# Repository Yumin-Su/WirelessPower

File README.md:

# WirelessPower
EAGLE PCB files for Wireless Power Team

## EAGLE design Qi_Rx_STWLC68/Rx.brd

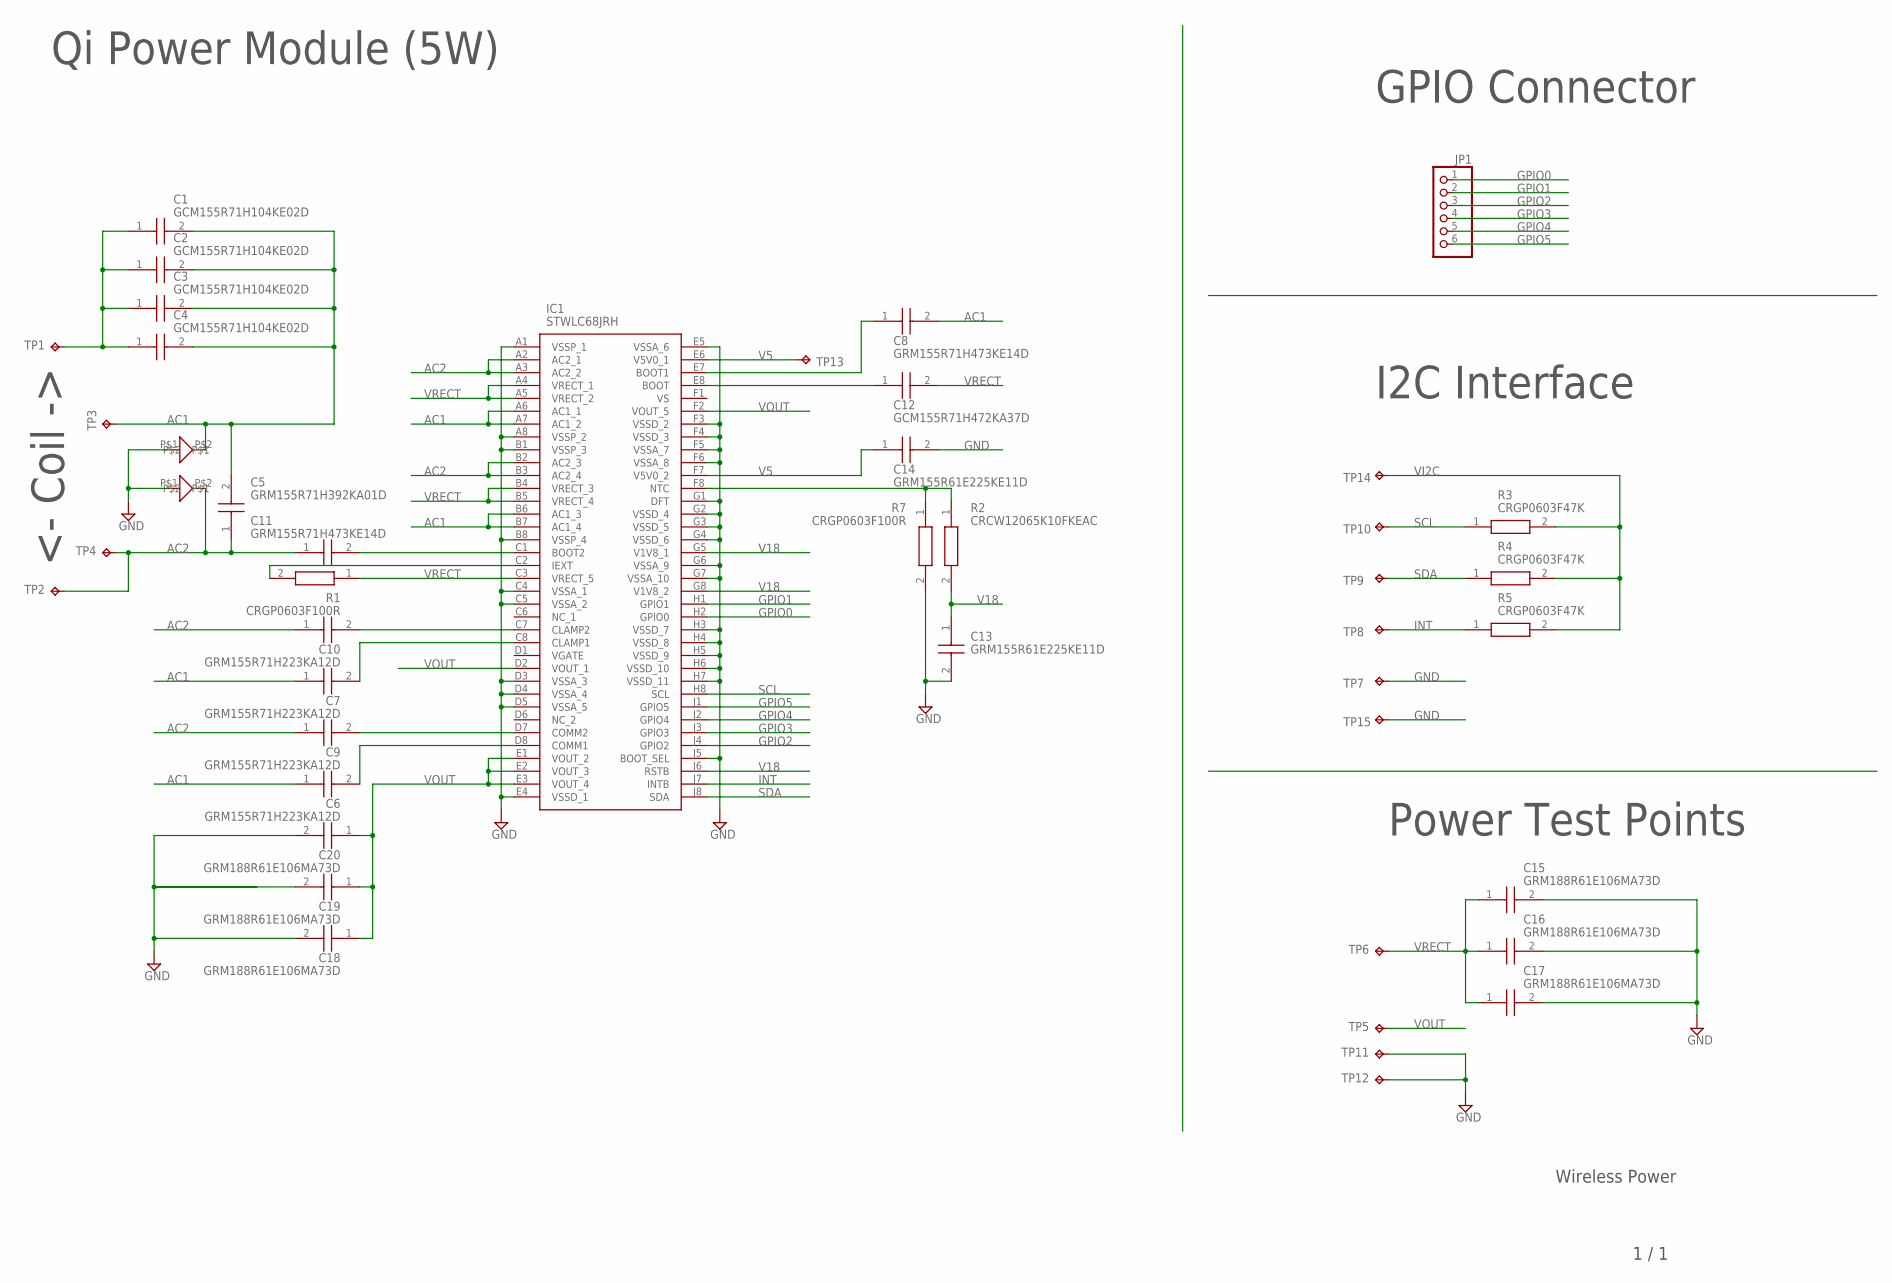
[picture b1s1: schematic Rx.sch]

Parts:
C1, C2, C3, C4: GCM155R71H104KE02D; CAPC1005X55N
C5: GRM155R71H392KA01D; CAPC1005X55N
C6, C7, C9, C10: GRM155R71H223KA12D; CAPC1005X55N
C8, C11: GRM155R71H473KE14D; CAPC1005X55N
C12: GCM155R71H472KA37D; CAPC1005X55N
C13, C14: GRM155R61E225KE11D; CAPC1005X55N
C15, C16, C17, C18, C19, C20: GRM188R61E106MA73D; CAPC1608X90N
IC1: STWLC68JRH; BGA72C40P9X9_441X376X58
JP1: PINHD-1X6; 1X06
R1, R7: CRGP0603F100R; RESC1608X55N
R2: CRCW12065K10FKEAC; RESC3216X60N
R3, R4, R5: CRGP0603F47K; RESC1608X55N
TP1, TP2, TP3, TP4, TP5, TP6, TP7, TP8, TP9, TP10, TP11, TP12, TP13, TP14, TP15: TPPAD1-13; P1-13
U$1, U$2: SMAJ16A

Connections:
AC1: C1.2, C2.2, C3.2, C4.2, C5.2, C6.1, C7.1, C8.2, IC1.A6 (AC1_1), IC1.A7 (AC1_2), IC1.B6 (AC1_3), IC1.B7 (AC1_4), TP3.TP, U$1.P$2
AC2: C5.1, C9.1, C10.1, C11.1, IC1.A2 (AC2_1), IC1.A3 (AC2_2), IC1.B2 (AC2_3), IC1.B3 (AC2_4), TP2.TP, TP4.TP, U$2.P$2
GND: C13.2, C14.2, C15.2, C16.2, C17.2, C18.2, C19.2, C20.2, IC1.A1 (VSSP_1), IC1.A8 (VSSP_2), IC1.B1 (VSSP_3), IC1.B8 (VSSP_4), IC1.C4 (VSSA_1), IC1.C5 (VSSA_2), IC1.D3 (VSSA_3), IC1.D4 (VSSA_4), IC1.D5 (VSSA_5), IC1.E4 (VSSD_1), IC1.E5 (VSSA_6), IC1.F3 (VSSD_2), IC1.F4 (VSSD_3), IC1.F5 (VSSA_7), IC1.F6 (VSSA_8), IC1.G1 (DFT), IC1.G2 (VSSD_4), IC1.G3 (VSSD_5), IC1.G4 (VSSD_6), IC1.G6 (VSSA_9), IC1.G7 (VSSA_10), IC1.H3 (VSSD_7), IC1.H4 (VSSD_8), IC1.H5 (VSSD_9), IC1.H6 (VSSD_10), IC1.H7 (VSSD_11), IC1.J5 (BOOT_SEL), R7.2, TP7.TP, TP11.TP, TP12.TP, TP15.TP, U$1.P$1, U$2.P$1
GPIO0: IC1.H2 (GPIO0), JP1.1
GPIO1: IC1.H1 (GPIO1), JP1.2
GPIO2: IC1.J4 (GPIO2), JP1.3
GPIO3: IC1.J3 (GPIO3), JP1.4
GPIO4: IC1.J2 (GPIO4), JP1.5
GPIO5: IC1.J1 (GPIO5), JP1.6
INT: IC1.J7 (INTB), R5.1, TP8.TP
unnamed: C6.2, IC1.D8 (COMM1)
unnamed: C7.2, IC1.C8 (CLAMP1)
unnamed: C8.1, IC1.E7 (BOOT1)
unnamed: C1.1, C2.1, C3.1, C4.1, TP1.TP
unnamed: C11.2, IC1.C1 (BOOT2)
unnamed: C10.2, IC1.C7 (CLAMP2)
unnamed: C9.2, IC1.D7 (COMM2)
unnamed: C12.1, IC1.E8 (BOOT)
unnamed: IC1.C2 (IEXT), R1.2
unnamed: IC1.F8 (NTC), R2.1, R7.1
SCL: IC1.H8 (SCL), R3.1, TP10.TP
SDA: IC1.J8 (SDA), R4.1, TP9.TP
V5: C14.1, IC1.E6 (V5V0_1), IC1.F7 (V5V0_2), TP13.TP
V18: C13.1, IC1.G5 (V1V8_1), IC1.G8 (V1V8_2), IC1.J6 (RSTB), R2.2
VI2C: R3.2, R4.2, R5.2, TP14.TP
VOUT: C18.1, C19.1, C20.1, IC1.D2 (VOUT_1), IC1.E1 (VOUT_2), IC1.E2 (VOUT_3), IC1.E3 (VOUT_4), IC1.F2 (VOUT_5), TP5.TP
VRECT: C12.2, C15.1, C16.1, C17.1, IC1.A4 (VRECT_1), IC1.A5 (VRECT_2), IC1.B4 (VRECT_3), IC1.B5 (VRECT_4), IC1.C3 (VRECT_5), R1.1, TP6.TP

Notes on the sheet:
1 / 1
Wireless Power
GPIO Connector
Qi Power Module (5W)
I2C Interface
Power Test Points
<- Coil ->

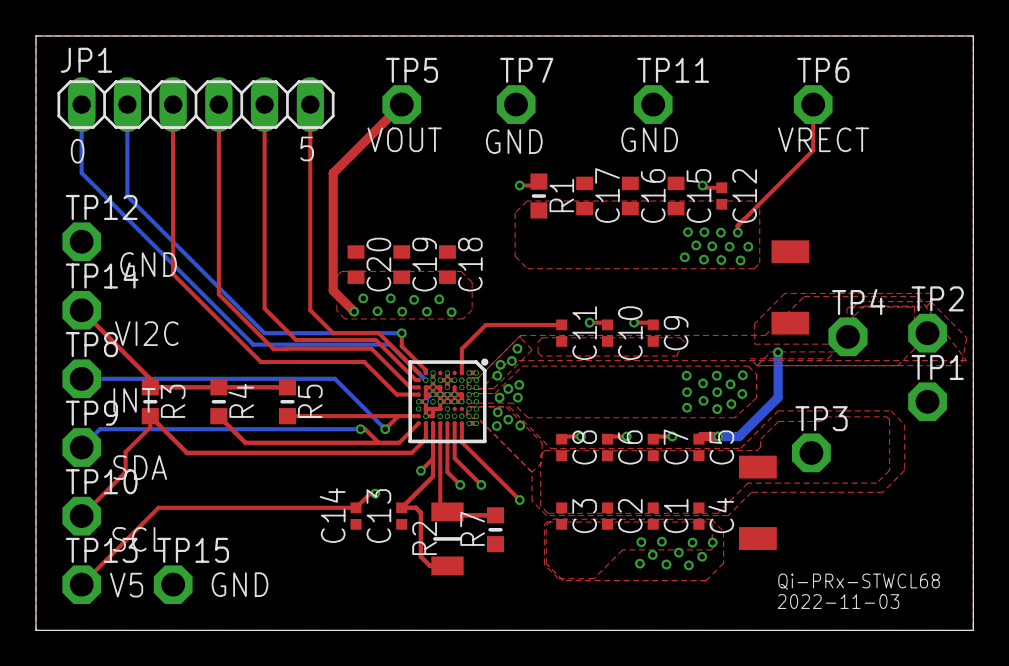
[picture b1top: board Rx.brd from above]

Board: 4 copper layers, 52.1 x 33.0 mm, 45 parts (0 on the bottom side), 27 nets.

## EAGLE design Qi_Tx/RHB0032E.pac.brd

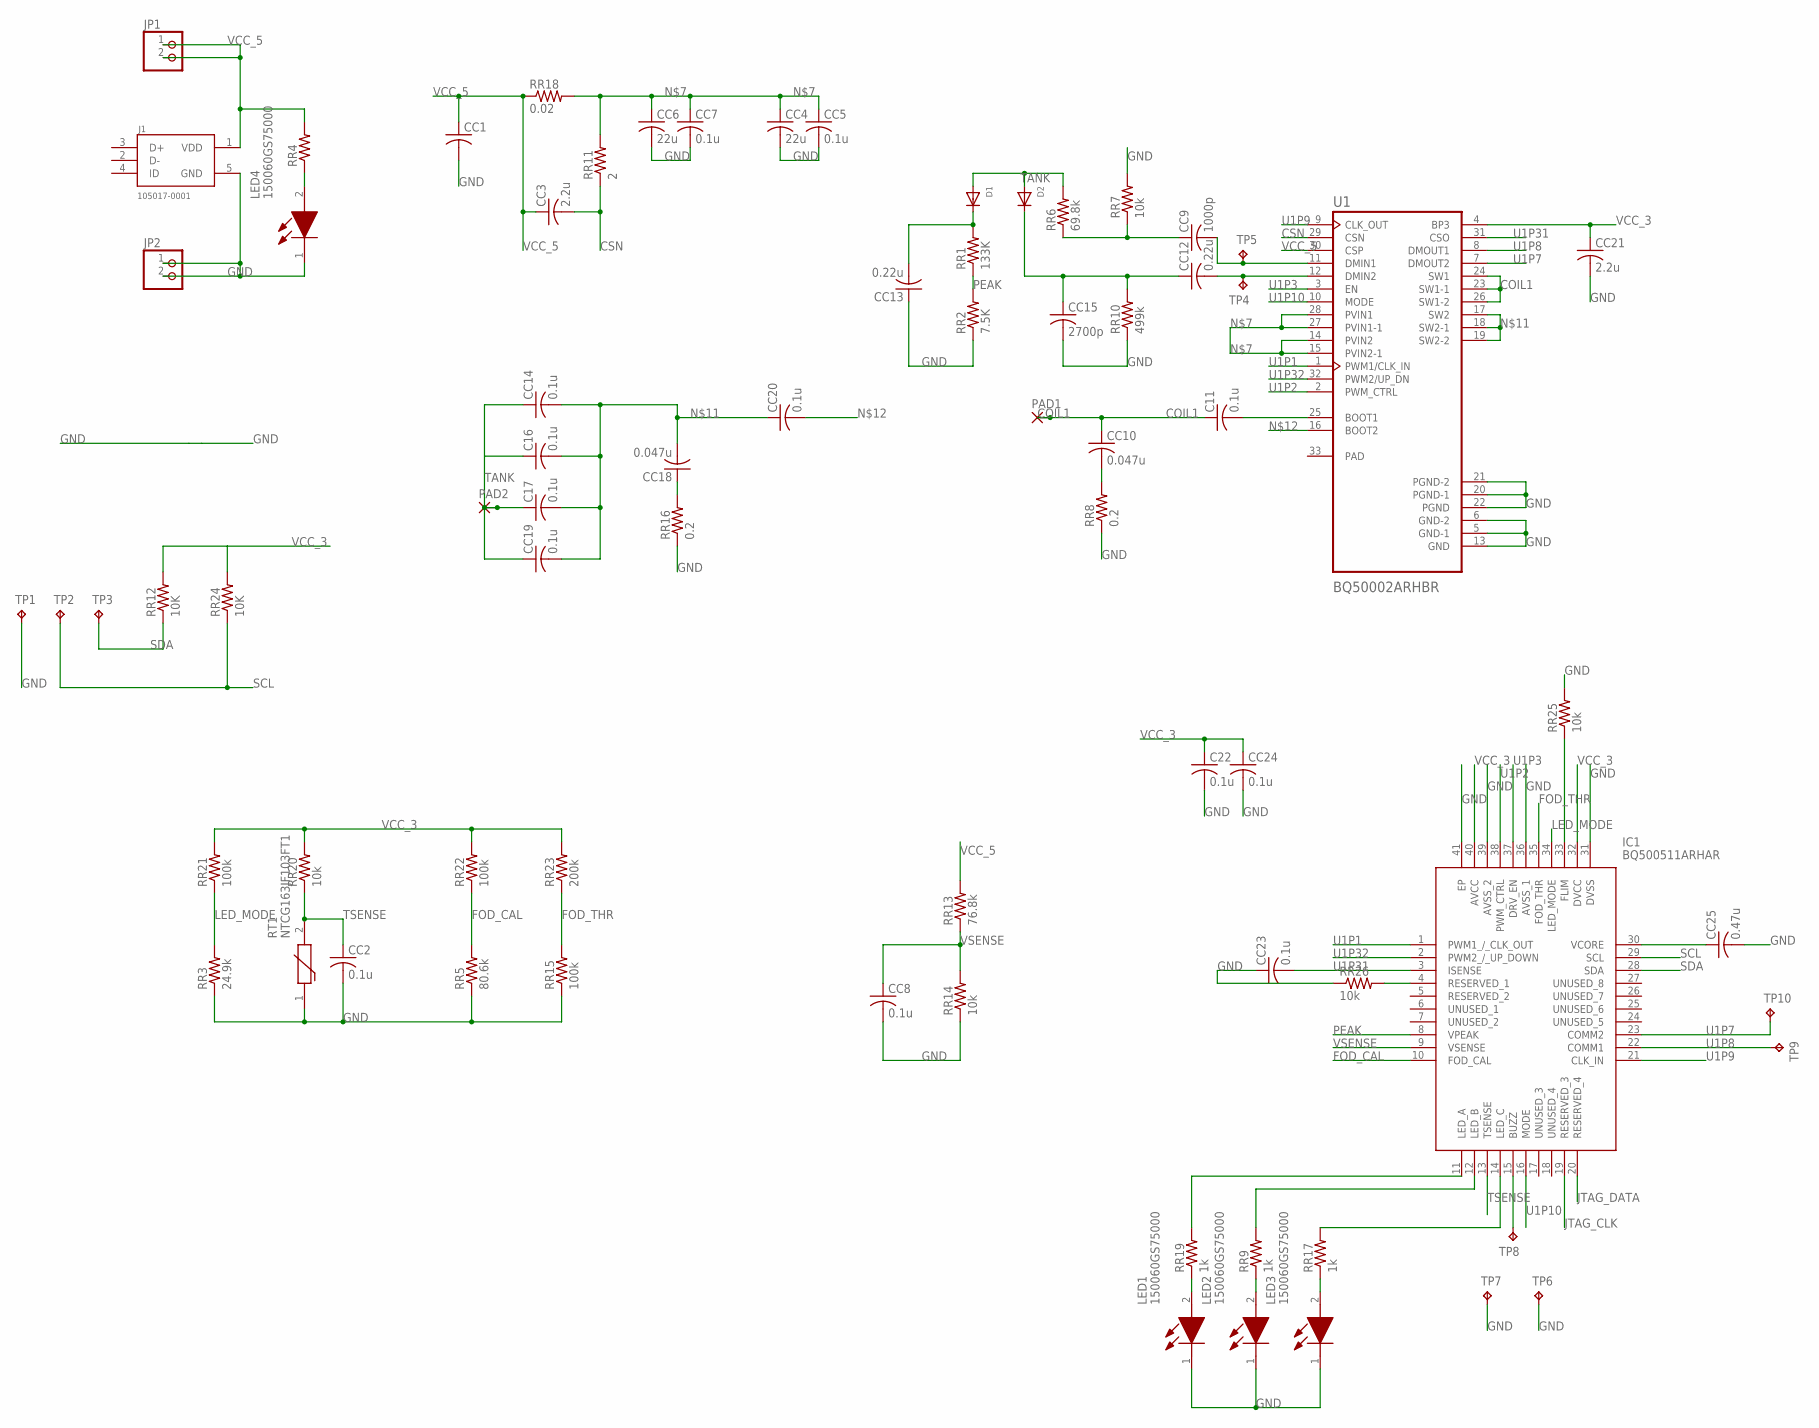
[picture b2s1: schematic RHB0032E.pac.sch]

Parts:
C11, C16, C17, C22: 0.1u; C0402
CC1: C-USC0402; C0402
CC2, CC5, CC7, CC8, CC14, CC19, CC20, CC23, CC24: 0.1u; C0402
CC3, CC21: 2.2u; C0402
CC4, CC6: 22u; C0402
CC9: 1000p; C0402
CC10, CC18: 0.047u; C0402
CC12, CC13: 0.22u; C0402
CC15: 2700p; C0402
CC25: 0.47u; C0402
D1, D2: DIODESOD-523; SOD-523
IC1: BQ500511ARHAR; QFN50P600X600X100-41N
J1: 105017-0001; MOLEX_105017-0001
JP1, JP2: PINHD-1X2; 1X02
LED1, LED2, LED3, LED4: 150060GS75000; LEDC1608X80N
PAD1, PAD2: SMD2; SMD1,27-2,54
RR1: 133K; R0603
RR2: 7.5K; R0603
RR3: 24.9k; R0603
RR4: R-US_R0603; R0603
RR5: 80.6k; R0603
RR6: 69.8k; R0603
RR7, RR14, RR20, RR25, RR26: 10k; R0603
RR8, RR16: 0.2; R0603
RR9, RR17, RR19: 1k; R0603
RR10: 499k; R0603
RR11: 2; R0603
RR12, RR24: 10K; R0603
RR13: 76.8k; R0603
RR15, RR21, RR22: 100k; R0603
RR18: 0.02; R0603
RR23: 200k; R0603
RT1: NTCG163JF103FT1; THRMC1608X90N
TP1, TP2, TP3, TP4, TP5, TP6, TP7, TP8, TP9, TP10: TPB1,27; B1,27
U1: BQ50002ARHBR; IC_ADS125H01IRHBT

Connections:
COIL1: C11.1, CC10.1, PAD1.1, U1.23 (SW1-1), U1.24 (SW1), U1.26 (SW1-2)
CSN: CC3.2, RR11.1, U1.29 (CSN)
FOD_CAL: IC1.10 (FOD_CAL), RR5.2, RR22.1
FOD_THR: IC1.35 (FOD_THR), RR15.2, RR23.1
GND: C22.2, CC1.2, CC2.2, CC4.2, CC5.2, CC6.2, CC7.2, CC8.2, CC13.1, CC15.2, CC21.2, CC23.1, CC24.2, CC25.2, IC1.31 (DVSS), IC1.36 (AVSS_1), IC1.39 (AVSS_2), IC1.41 (EP), J1.5 (GND), JP2.1, JP2.2, LED1.1 (K), LED2.1 (K), LED3.1 (K), LED4.1 (K), RR2.1, RR3.1, RR5.1, RR7.2, RR8.1, RR10.1, RR14.1, RR15.1, RR16.1, RR25.2, RR26.1, RT1.1, TP1.TP, TP6.TP, TP7.TP, U1.5 (GND-1), U1.6 (GND-2), U1.13 (GND), U1.20 (PGND-1), U1.21 (PGND-2), U1.22 (PGND)
JTAG_CLK: IC1.19 (RESERVED_3)
JTAG_DATA: IC1.20 (RESERVED_4)
LED_MODE: IC1.34 (LED_MODE), RR3.2, RR21.1
unnamed: CC12.2, TP4.TP, U1.12 (DMIN2)
unnamed: CC12.1, CC15.1, D2.K (C), RR10.2
unnamed: CC13.2, D1.K (C), RR1.2
unnamed: CC9.2, TP5.TP, U1.11 (DMIN1)
unnamed: CC9.1, RR6.1, RR7.1
unnamed: CC4.1, CC5.1, CC6.1, CC7.1, RR11.2, RR18.2, U1.14 (PVIN2), U1.15 (PVIN2-1), U1.27 (PVIN1-1), U1.28 (PVIN1)
unnamed: IC1.15 (BUZZ), TP8.TP
unnamed: C11.2, U1.25 (BOOT1)
unnamed: CC10.2, RR8.2
unnamed: C16.2, C17.2, CC14.2, CC18.2, CC19.2, CC20.1, U1.17 (SW2), U1.18 (SW2-1), U1.19 (SW2-2)
unnamed: CC20.2, U1.16 (BOOT2)
unnamed: CC25.1, IC1.30 (VCORE)
unnamed: LED1.2 (A), RR19.1
unnamed: CC18.1, RR16.2
unnamed: LED2.2 (A), RR9.1
unnamed: LED3.2 (A), RR17.1
unnamed: IC1.33 (FLIM), RR25.1
unnamed: IC1.11 (LED_A), RR19.2
unnamed: IC1.12 (LED_B), RR9.2
unnamed: IC1.14 (LED_C), RR17.2
unnamed: IC1.4 (RESERVED_1), RR26.2
unnamed: LED4.2 (A), RR4.1
PEAK: IC1.8 (VPEAK), RR1.1, RR2.2
SCL: IC1.29 (SCL), RR24.1, TP2.TP
SDA: IC1.28 (SDA), RR12.1, TP3.TP
TANK: C16.1, C17.1, CC14.1, CC19.1, D1.A, D2.A, PAD2.1, RR6.2
TSENSE: CC2.1, IC1.13 (TSENSE), RR20.1, RT1.2
U1P1: IC1.1 (PWM1_/_CLK_OUT), U1.1 (PWM1/CLK_IN)
U1P2: IC1.38 (PWM_CTRL), U1.2 (PWM_CTRL)
U1P3: IC1.37 (DRV_EN), U1.3 (EN)
U1P7: IC1.23 (COMM2), TP10.TP, U1.7 (DMOUT2)
U1P8: IC1.22 (COMM1), TP9.TP, U1.8 (DMOUT1)
U1P9: IC1.21 (CLK_IN), U1.9 (CLK_OUT)
U1P10: IC1.16 (MODE), U1.10 (MODE)
U1P31: CC23.2, IC1.3 (ISENSE), U1.31 (CSO)
U1P32: IC1.2 (PWM2_/_UP_DOWN), U1.32 (PWM2/UP_DN)
VCC_3: C22.1, CC21.1, CC24.1, IC1.32 (DVCC), IC1.40 (AVCC), RR12.2, RR20.2, RR21.2, RR22.2, RR23.2, RR24.2, U1.4 (BP3)
VCC_5: CC1.1, CC3.1, J1.1 (VDD), JP1.1, JP1.2, RR4.2, RR13.2, RR18.1, U1.30 (CSP)
VSENSE: CC8.1, IC1.9 (VSENSE), RR13.1, RR14.2

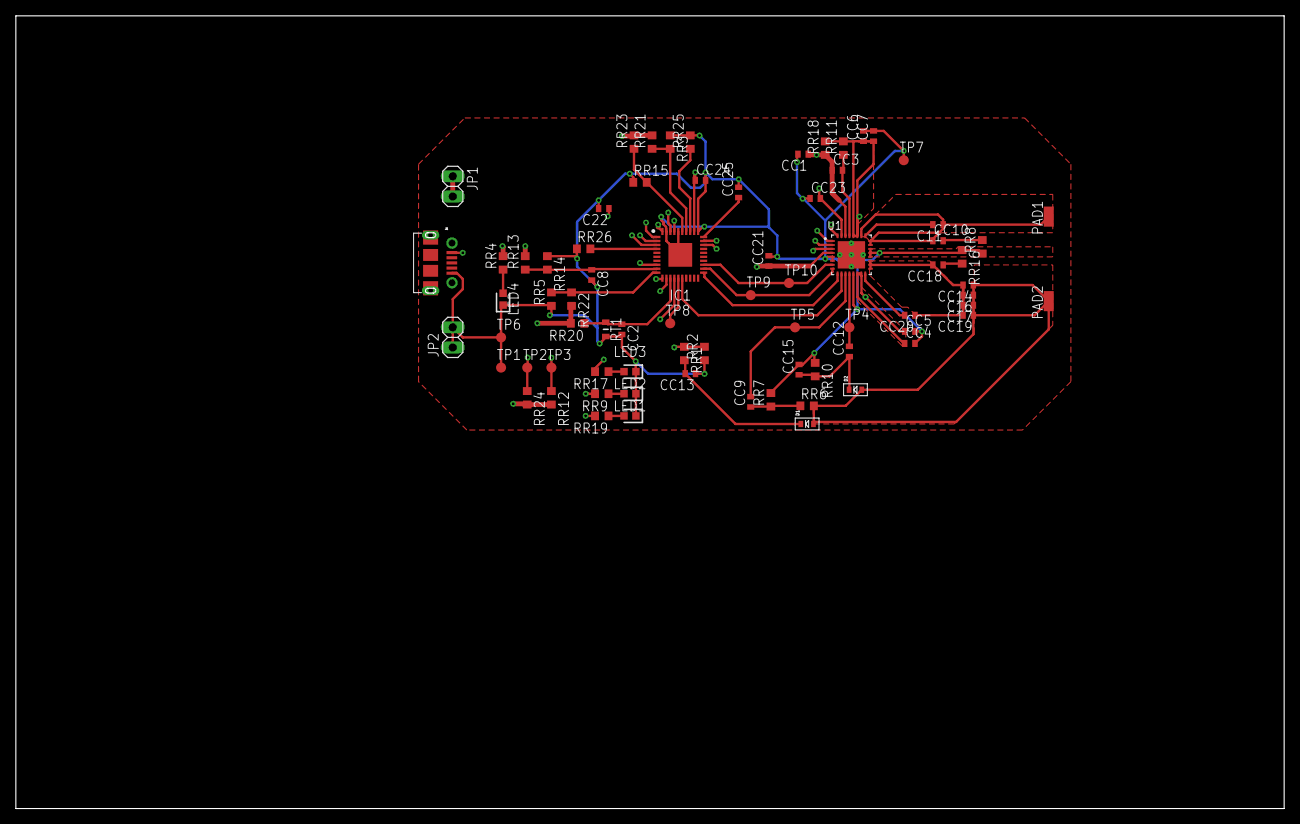
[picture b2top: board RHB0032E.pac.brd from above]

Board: 4 copper layers, 160.0 x 100.0 mm, 75 parts (0 on the bottom side), 45 nets.

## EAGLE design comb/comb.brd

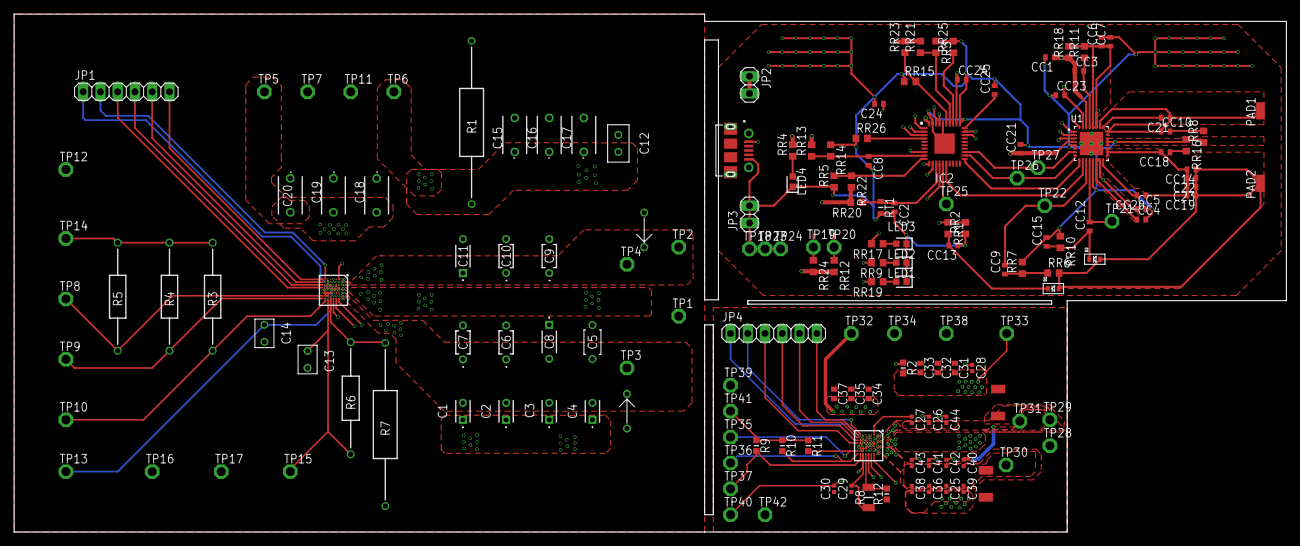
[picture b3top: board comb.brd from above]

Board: 4 copper layers, 187.1 x 76.2 mm, 167 parts (0 on the bottom side), 99 nets.

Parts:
C1, C2, C3, C4: K104K15X7RF5UL2
C5: RCE5C1H392J0K1H03B; RCER71H104K0K1H03B
C6, C7, C9, C10: K223K15X7RF53H5G
C8, C11: K473K15X0UH53H5H
C12: RDE5C2J472J2K1H03B; RCE5C1H104J2A2H03B
C13, C14: RHS7G2A222J1DGH01A; RHS7G2A182J1A2H01B
C15, C16, C17, C18, C19, C20: FG26X7R1E106KRT06; FG26
C21, C22, C23, C24: 0.1u; C0402
C25, C36, C38, C39: GCM155R71H104KE02D; CAPC1005X55N
C26, C41, C42, C44: GRM155R71H223KA12D; CAPC1005X55N
C27, C43: GRM155R71H473KE14D; CAPC1005X55N
C28: GCM155R71H472KA37D; CAPC1005X55N
C29, C30: GRM155R61E225KE11D; CAPC1005X55N
C31, C32, C33, C34, C35, C37: GRM188R61E106MA73D; CAPC1608X90N
C40: GRM155R71H392KA01D; CAPC1005X55N
CC1: C0402
CC2, CC5, CC7, CC8, CC14, CC19, CC20, CC23, CC24: 0.1u; C0402
CC3, CC21: 2.2u; C0402
CC4, CC6: 22u; C0402
CC9: 1000p; C0402
CC10, CC18: 0.047u; C0402
CC12, CC13: 0.22u; C0402
CC15: 2700p; C0402
CC25: 0.47u; C0402
D1, D2: SOD-523
IC1, IC3: STWLC68JRH; BGA72C40P9X9_441X376X58
IC2: BQ500511ARHAR; QFN50P600X600X100-41N
J1: 105017-0001; MOLEX_105017-0001
JP1, JP4: 1X06
JP2, JP3: 1X02
LED1, LED2, LED3, LED4: 150060GS75000; LEDC1608X80N
PAD1, PAD2: SMD1,27-2,54
R1, R7: EP1WS100RJ; RESAD2400W54L1000D350
R2, R12: CRGP0603F100R; RESC1608X55N
R3, R4, R5: MFR-25FRF52-47K; RESAD1590W60L630D240
R6: MRS25000C5101FCT00; RESAD1650W60L650D250
R8: CRCW12065K10FKEAC; RESC3216X60N
R9, R10, R11: CRGP0603F47K; RESC1608X55N
RR1: 133K; R0603
RR2: 7.5K; R0603
RR3: 24.9k; R0603
RR4: R0603
RR5: 80.6k; R0603
RR6: 69.8k; R0603
RR7, RR14, RR20, RR25, RR26: 10k; R0603
RR8, RR16: 0.2; R0603
RR9, RR17, RR19: 1k; R0603
RR10: 499k; R0603
RR11: 2; R0603
RR12, RR24: 10K; R0603
RR13: 76.8k; R0603
RR15, RR21, RR22: 100k; R0603
RR18: 0.02; R0603
RR23: 200k; R0603
RT1: NTCG163JF103FT1; THRMC1608X90N
TP1, TP2, TP3, TP4, TP5, TP6, TP7, TP8, TP9, TP10, TP11, TP12, TP13, TP14, TP15, TP16, TP17, TP18, TP19, TP20, TP21, TP22, TP23, TP24, TP25, TP26, TP27, TP28, TP29, TP30, TP31, TP32, TP33, TP34, TP35, TP36, TP37, TP38, TP39, TP40, TP41, TP42: TPPAD1-13; P1-13
U1: BQ50002ARHBR; IC_ADS125H01IRHBT
U$1, U$2: SA16A-E3/54
U$3, U$4: SMAJ16A

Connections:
AC1: C1.2, C2.2, C3.2, C4.2, C5.2, C6.1, C7.1, C8.2, IC1.A6, IC1.A7, IC1.B6, IC1.B7, TP3.TP, U$1.P$2
AC2: C5.1, C9.1, C10.1, C11.1, IC1.A2, IC1.A3, IC1.B2, IC1.B3, TP2.TP, TP4.TP, U$2.P$2
AC3: C25.2, C36.2, C38.2, C39.2, C40.2, C41.1, C42.1, C43.2, IC3.A6, IC3.A7, IC3.B6, IC3.B7, TP30.TP, U$3.P$2
AC4: C26.1, C27.1, C40.1, C44.1, IC3.A2, IC3.A3, IC3.B2, IC3.B3, TP29.TP, TP31.TP, U$4.P$2
COIL1: C21.1, CC10.1, PAD1.1, U1.23, U1.24, U1.26
CSN: CC3.2, RR11.1, U1.29
FOD_CAL: IC2.10, RR5.2, RR22.1
FOD_THR: IC2.35, RR15.2, RR23.1
GND: C13.1, C14.2, C15.2, C16.2, C17.2, C18.1, C19.1, C20.1, IC1.A1, IC1.A8, IC1.B1, IC1.B8, IC1.C4, IC1.C5, IC1.D3, IC1.D4, IC1.D5, IC1.E4, IC1.E5, IC1.F3, IC1.F4, IC1.F5, IC1.F6, IC1.G1, IC1.G2, IC1.G3, IC1.G4, IC1.G6, IC1.G7, IC1.H3, IC1.H4, IC1.H5, IC1.H6, IC1.H7, IC1.J5, R7.1, TP7.TP, TP11.TP, TP12.TP, TP16.TP, TP17.TP, U$1.P$1, U$2.P$1
GND1: C24.2, CC1.2, CC2.2, CC4.2, CC5.2, CC6.2, CC7.2, CC8.2, CC13.1, CC15.2, CC21.2, CC23.1, CC24.2, CC25.2, IC2.31, IC2.36, IC2.39, IC2.41, J1.5, JP3.1, JP3.2, LED1.1, LED2.1, LED3.1, LED4.1, RR2.1, RR3.1, RR5.1, RR7.2, RR8.1, RR10.1, RR14.1, RR15.1, RR16.1, RR25.2, RR26.1, RT1.1, TP18.TP, TP23.TP, TP24.TP, U1.5, U1.6, U1.13, U1.20, U1.21, U1.22
GND2: C29.2, C30.2, C31.2, C32.2, C33.2, C34.2, C35.2, C37.2, IC3.A1, IC3.A8, IC3.B1, IC3.B8, IC3.C4, IC3.C5, IC3.D3, IC3.D4, IC3.D5, IC3.E4, IC3.E5, IC3.F3, IC3.F4, IC3.F5, IC3.F6, IC3.G1, IC3.G2, IC3.G3, IC3.G4, IC3.G6, IC3.G7, IC3.H3, IC3.H4, IC3.H5, IC3.H6, IC3.H7, IC3.J5, R12.2, TP34.TP, TP38.TP, TP39.TP, TP42.TP, U$3.P$1, U$4.P$1
GPIO0: IC1.H2, JP1.1
GPIO1: IC1.H1, JP1.2
GPIO2: IC1.J4, JP1.3
GPIO3: IC1.J3, JP1.4
GPIO4: IC1.J2, JP1.5
GPIO5: IC1.J1, JP1.6
GPIO6: IC3.H1, JP4.2
GPIO7: IC3.J1, JP4.6
GPIO8: IC3.J2, JP4.5
GPIO9: IC3.J3, JP4.4
GPIO10: IC3.J4, JP4.3
GPIO11: IC3.H2, JP4.1
INT: IC1.J7, R5.1, TP8.TP
INT1: IC3.J7, R11.1, TP35.TP
LED_MODE: IC2.34, RR3.2, RR21.1
unnamed: C6.2, IC1.D8
unnamed: C7.2, IC1.C8
unnamed: C8.1, IC1.E7
unnamed: C1.1, C2.1, C3.1, C4.1, TP1.TP
unnamed: C11.2, IC1.C1
unnamed: C10.2, IC1.C7
unnamed: C9.2, IC1.D7
unnamed: C12.1, IC1.E8
unnamed: IC1.C2, R1.2
unnamed: IC1.F8, R6.2, R7.2
unnamed: R3.2, R4.2, R5.2, TP14.TP
unnamed: CC12.2, TP21.TP, U1.12
unnamed: CC12.1, CC15.1, D2.K, RR10.2
unnamed: CC9.2, TP22.TP, U1.11
unnamed: CC9.1, RR6.1, RR7.1
unnamed: CC13.2, D1.K, RR1.2
unnamed: CC4.1, CC5.1, CC6.1, CC7.1, RR11.2, RR18.2, U1.14, U1.15, U1.27, U1.28
unnamed: C21.2, U1.25
unnamed: CC10.2, RR8.2
unnamed: C22.2, C23.2, CC14.2, CC18.2, CC19.2, CC20.1, U1.17, U1.18, U1.19
unnamed: CC20.2, U1.16
unnamed: CC18.1, RR16.2
unnamed: CC25.1, IC2.30
unnamed: IC2.15, TP25.TP
unnamed: LED1.2, RR19.1
unnamed: LED2.2, RR9.1
unnamed: LED3.2, RR17.1
unnamed: IC2.11, RR19.2
unnamed: IC2.12, RR9.2
unnamed: IC2.14, RR17.2
unnamed: IC2.33, RR25.1
unnamed: IC2.4, RR26.2
unnamed: LED4.2, RR4.1
unnamed: C41.2, IC3.D8
unnamed: C42.2, IC3.C8
unnamed: C43.1, IC3.E7
unnamed: C25.1, C36.1, C38.1, C39.1, TP28.TP
unnamed: C27.2, IC3.C1
unnamed: C26.2, IC3.C7
unnamed: C44.2, IC3.D7
unnamed: C28.1, IC3.E8
unnamed: IC3.C2, R2.2
unnamed: IC3.F8, R8.1, R12.1
PEAK: IC2.8, RR1.1, RR2.2
SCL: IC1.H8, R3.1, TP10.TP
SCL1: IC2.29, RR24.1, TP19.TP
SCL2: IC3.H8, R9.1, TP37.TP
SDA: IC1.J8, R4.1, TP9.TP
SDA1: IC2.28, RR12.1, TP20.TP
SDA2: IC3.J8, R10.1, TP36.TP
TANK: C22.1, C23.1, CC14.1, CC19.1, D1.A, D2.A, PAD2.1, RR6.2
TSENSE: CC2.1, IC2.13, RR20.1, RT1.2
U1P1: IC2.1, U1.1
U1P2: IC2.38, U1.2
U1P3: IC2.37, U1.3
U1P7: IC2.23, TP27.TP, U1.7
U1P8: IC2.22, TP26.TP, U1.8
U1P9: IC2.21, U1.9
U1P10: IC2.16, U1.10
U1P31: CC23.2, IC2.3, U1.31
U1P32: IC2.2, U1.32
V1: C29.1, IC3.G5, IC3.G8, IC3.J6, R8.2
V2: C30.1, IC3.E6, IC3.F7, TP40.TP
V5: C14.1, IC1.E6, IC1.F7, TP13.TP
V18: C13.2, IC1.G5, IC1.G8, IC1.J6, R6.1, TP15.TP
VCC_3: C24.1, CC21.1, CC24.1, IC2.32, IC2.40, RR12.2, RR20.2, RR21.2, RR22.2, RR23.2, RR24.2, U1.4
VCC_5: CC1.1, CC3.1, J1.1, JP2.1, JP2.2, RR4.2, RR13.2, RR18.1, U1.30
VI2C: R9.2, R10.2, R11.2, TP41.TP
VOUT: C18.2, C19.2, C20.2, IC1.D2, IC1.E1, IC1.E2, IC1.E3, IC1.F2, TP5.TP
VOUT1: C34.1, C35.1, C37.1, IC3.D2, IC3.E1, IC3.E2, IC3.E3, IC3.F2, TP32.TP
VRECT: C12.2, C15.1, C16.1, C17.1, IC1.A4, IC1.A5, IC1.B4, IC1.B5, IC1.C3, R1.1, TP6.TP
VRECT1: C28.2, C31.1, C32.1, C33.1, IC3.A4, IC3.A5, IC3.B4, IC3.B5, IC3.C3, R2.1, TP33.TP
VSENSE: CC8.1, IC2.9, RR13.1, RR14.2

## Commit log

2022-10-24 Initial Rx PCB layout
2022-10-28 Complete SMD layout
2022-10-28 Replace surface-mount devices with through-hole ones
2022-11-03 Rx through-hole cleanup
2022-11-03 Rx surface-mount cleanup
2022-11-04 Create tx
2022-11-04 Combine PCBs
2022-11-04 Clean up
2022-11-04 Generate Gerber files with Seeed Fusion cam
